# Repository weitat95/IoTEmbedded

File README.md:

View this project on [CADLAB.io](https://cadlab.io/project/1460). 

Project Files for ARM CORTEX M4, TM4C1234GH
Compiled and Programmed with Keil UVision 4

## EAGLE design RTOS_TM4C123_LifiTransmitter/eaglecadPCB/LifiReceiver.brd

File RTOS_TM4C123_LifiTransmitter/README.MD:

*  This is used for my BEng Honours 4th Year Project in The University of Edinburgh

*  Title: Demonstration of Visible Light Communication 
*
*  Author: Wei Tat Lee
*  Thesis Supervisor: Dr. Jonathan Terry

* This project builts on a previously developed RTOS in one of my classes(EE445M-Real-Time OS) in University of Texas, At Austin, taught by  Dr.Jonathan W. Valvano

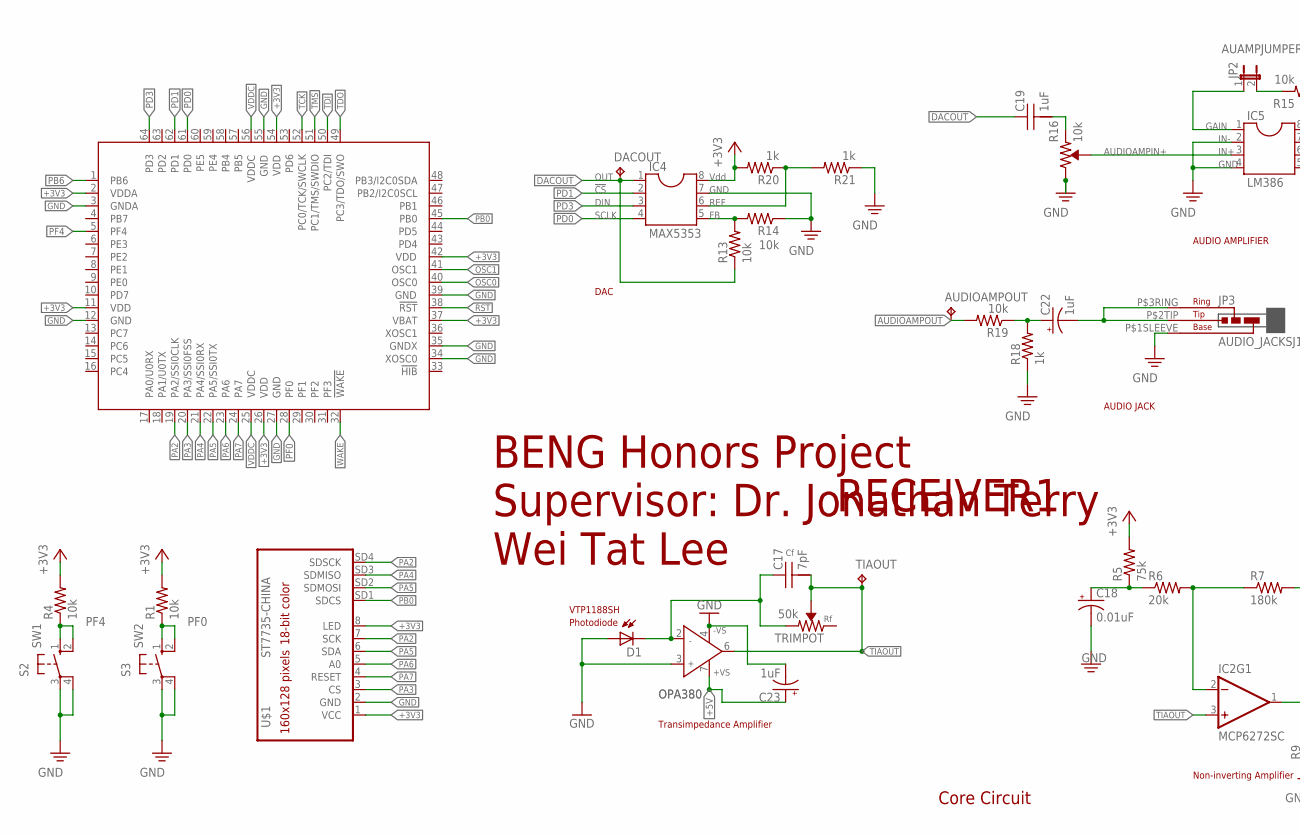
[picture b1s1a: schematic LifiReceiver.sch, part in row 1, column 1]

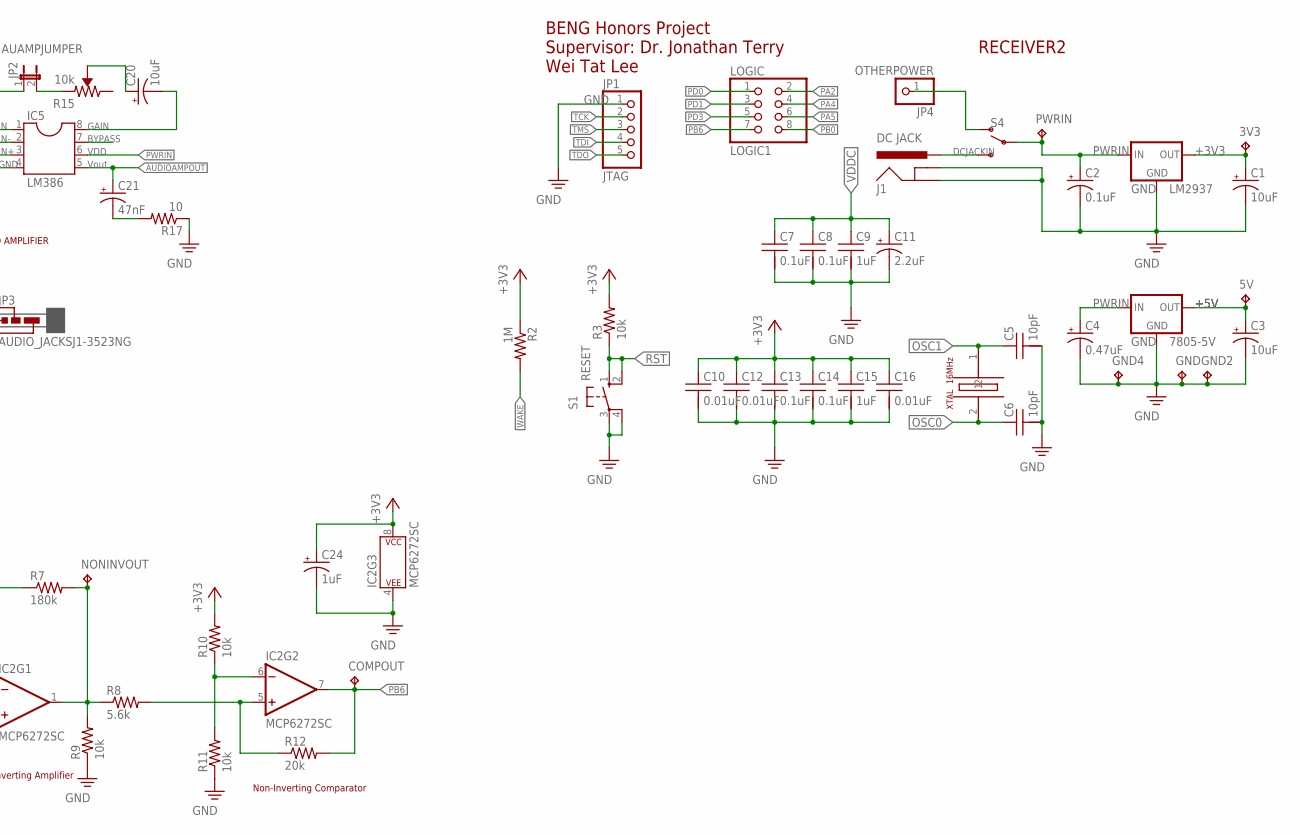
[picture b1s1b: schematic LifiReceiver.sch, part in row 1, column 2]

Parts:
3V3, 5V: TP_KEYSTONE500X; P1.1MM
7805-5V: 78XXS
AUDIOAMPOUT: TP_KEYSTONE500X; P1.1MM
C1, C3, C20: 10uF; CAP200MILPOLARIZED
C2: 0.1uF; CAP200MILPOLARIZED
C4: 0.47uF; CAP200MILPOLARIZED
C5, C6: 10pF; CAP100MIL
C7, C8, C13, C14: 0.1uF; CAP100MIL
C9, C15: 1uF; CAP100MIL
C10, C12, C16: 0.01uF; CAP100MIL
C11: 2.2uF; CAP200MILPOLARIZED
C17: 7pF; CAP200MIL
C18: 0.01uF; CAP200MILPOLARIZED
C19: 1uF; CAP200MIL
C21: 47nF; CAP200MILPOLARIZED
C22, C23, C24: 1uF; CAP200MILPOLARIZED
COMPOUT: TP_KEYSTONE500X; P1.1MM
D1: PHOTODIODE1X02THROUGH; 1X02_LOCK
DACOUT: TP_KEYSTONE500X; P1.1MM
GND, GND2, GND4: TP_KEYSTONE500X; P1.1MM
IC1: TM4C123[1,3,B]XXPM; PM_S-PQFP-G64
IC2: MCP6272SC; SOCKET-08
IC4: MAX5353; SOCKET-08
IC5: LM386; SOCKET-08
J1: DC JACK; POWER_JACK_PTH_BREAD
JP1: JTAG; 1X05
JP2: AUAMPJUMPER; 1X02
JP3: AUDIO_JACKSJ1-3523NG; JACK-SJ1-3523NG
JP4: OTHERPOWER; 1X01
LM2937: 78XXS
LOGIC: LOGIC1; 2X04
NONINVOUT: TP_KEYSTONE500X; P1.1MM
OPA380: AD820RM; MSOP08; MPN OPA380
PWRIN: TP_KEYSTONE500X; P1.1MM
R1, R3, R4, R9, R10, R11, R13, R14, R19: 10k; RES400MIL
R2: 1M; RES400MIL
R5: 75k; RES400MIL
R6, R12: 20k; RES400MIL
R7: 180k; RES400MIL
R8: 5.6k; RES400MIL
R15, R16: 10k; TRIM-SUNTAN3362P
R17: 10; RES400MIL
R18, R20, R21: 1k; RES400MIL
S1: RESET; B3F-10XX
S2: SW1; B3F-10XX
S3: SW2; B3F-10XX
S4: SWITCH-SPDT-PTH-11.6X4.0MM; SWITCH_SPDT_PTH_11.6X4.0MM
TIAOUT: TP_KEYSTONE500X; P1.1MM
TRIMPOT: 50k; TRIM-SUNTAN3362P
U$1: ST7735-CHINA
XTAL: 16MHz; XTAL

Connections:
+3V3: 3V3.TP, C1.+, C10.1, C12.1, C13.1, C14.1, C15.1, C16.1, C24.+, IC1.2 (VDDA), IC1.11 (VDD), IC1.26 (VDD), IC1.37 (VBAT), IC1.42 (VDD), IC1.54 (VDD), IC2.8 (P$V+), IC4.8, LM2937.OUT, R1.2, R2.1, R3.2, R4.2, R5.2, R10.2, R20.2, U$1.1 (VCC), U$1.8 (LED)
+5V: 5V.TP, 7805-5V.OUT, C3.+, C23.+, OPA380.7 (+VS)
AUAMPJUMP3: JP2.2, R15.P$1 (CCW)
AUAMPJUNCT1: C19.2, R16.P$1 (CCW)
AUAMPJUNCT2: C21.-, R17.2
AUAMPJUNCT4: C20.+, R15.P$2M (WIPER)
AUDIOAMPIN+: IC5.3, R16.P$2M (WIPER)
AUDIOAMPOUT: AUDIOAMPOUT.TP, C21.+, IC5.5, R19.2
AUDIOBYPASS: IC5.7
AUJACKJUNCT1: C22.+, R18.2, R19.1
AUJACKRINGTIP: C22.-, JP3.P$2TIP (TIP), JP3.P$3RING (RING)
COMPIN-: IC2.5 (+IN), R8.2, R12.1
COMPREF: IC2.6 (-IN), R10.1, R11.2
DACFB: IC4.5, R13.2, R14.2
DACOUT: C19.1, DACOUT.TP, IC4.1, R13.1
DACREF: IC4.6, R20.1, R21.2
DCJACKIN: J1.PWR, S4.3 (S)
GAIN1: IC5.1, JP2.1
GAIN2: C20.-, IC5.8
GND: 7805-5V.GND, C1.-, C2.-, C3.-, C4.-, C5.2, C6.2, C7.2, C8.2, C9.2, C10.2, C11.-, C12.2, C13.2, C14.2, C15.2, C16.2, C18.-, C23.-, C24.-, D1.1+ (A), GND.TP, GND2.TP, GND4.TP, IC1.3 (GNDA), IC1.12 (GND), IC1.27 (GND), IC1.34 (XOSC0), IC1.35 (GNDX), IC1.39 (GND), IC1.55 (GND), IC2.4 (P$V-), IC4.7, IC5.2, IC5.4, J1.GND, J1.GNDBREAK, JP1.1, JP3.P$1SLEEVE (BASE), LM2937.GND, OPA380.3 (IN+), OPA380.4 (-VS), R9.1, R11.1, R14.1, R16.P$3 (CW), R17.1, R18.1, R21.1, S1.3, S1.4 (P1), S2.3, S2.4 (P1), S3.3, S3.4 (P1), U$1.2 (GND)
NONINV-: IC2.2 (-IN), R6.2, R7.1
NONINVAMPJUNT1: C18.+, R5.1, R6.1
NONINVOUT: IC2.1 (OUT), NONINVOUT.TP, R7.2, R8.1, R9.2
OSC0: C6.1, IC1.40 (OSC0), XTAL.2
OSC1: C5.1, IC1.41 (OSC1), XTAL.1
OTHERPOWER: JP4.1, S4.1 (O)
PA2: IC1.19 (PA2/SSI0CLK), LOGIC.2, U$1.7 (SCK), U$1.SD4 (SDSCK)
PA3: IC1.20 (PA3/SSI0FSS), U$1.3 (CS)
PA4: IC1.21 (PA4/SSI0RX), LOGIC.4, U$1.SD3 (SDMISO)
PA5: IC1.22 (PA5/SSI0TX), LOGIC.6, U$1.6 (SDA), U$1.SD2 (SDMOSI)
PA6: IC1.23 (PA6), U$1.5 (A0)
PA7: IC1.24 (PA7), U$1.4 (RESET)
PB0: IC1.45 (PB0), LOGIC.8, U$1.SD1 (SDCS)
PB6: COMPOUT.TP, IC1.1 (PB6), IC2.7 (OUT), LOGIC.7, R12.2
PD0: IC1.61 (PD0), IC4.4, LOGIC.1
PD1: IC1.62 (PD1), IC4.2, LOGIC.3
PD3: IC1.64 (PD3), IC4.3, LOGIC.5
PF0: IC1.28 (PF0), R1.1, S3.1 (S), S3.2 (S1)
PF4: IC1.5 (PF4), R4.1, S2.1 (S), S2.2 (S1)
PHOTODIODECAT: C17.1, D1.2 (C), OPA380.2 (IN-), TRIMPOT.P$1 (CCW)
PWRIN: 7805-5V.IN, C2.+, C4.+, IC5.6, LM2937.IN, PWRIN.TP, S4.2
RST: IC1.38 (!RST), R3.1, S1.1 (S), S1.2 (S1)
TCK: IC1.52 (PC0/TCK/SWCLK), JP1.2
TDI: IC1.50 (PC2/TDI), JP1.4
TDO: IC1.49 (PC3/TDO/SWO), JP1.5
TIAOUT: C17.2, IC2.3 (+IN), OPA380.6 (OUT), TIAOUT.TP, TRIMPOT.P$2M (WIPER)
TMS: IC1.51 (PC1/TMS/SWDIO), JP1.3
VDDC: C7.1, C8.1, C9.1, C11.+, IC1.25 (VDDC), IC1.56 (VDDC)
WAKE: IC1.32 (!WAKE), R2.2

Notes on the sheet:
BENG Honors Project Supervisor: Dr. Jonathan Terry Wei Tat Lee
Transimpedance Amplifier
Non-inverting Amplifier
Non-Inverting Comparator
Photodiode
VTP1188SH
Core Circuit
!CS
DIN
SCLK
OUT
Vdd
GND
REF
DAC
BYPASS
IN-
IN+
GAIN
VDD
Vout
AUDIO AMPLIFIER
AUDIO JACK
RECEIVER2
RECEIVER1

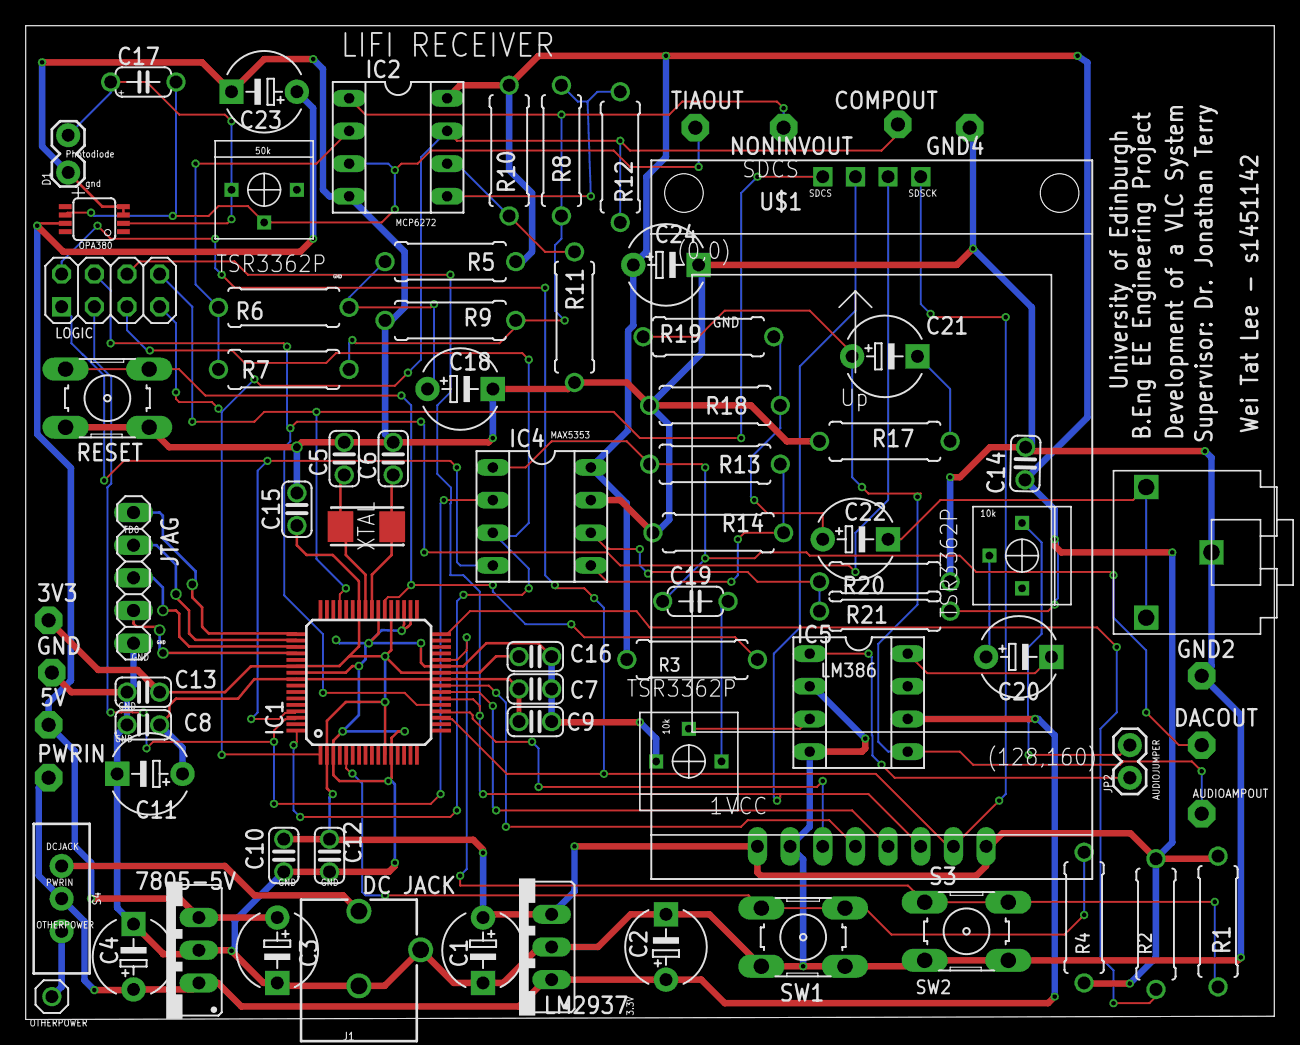
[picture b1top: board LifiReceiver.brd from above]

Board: 2 copper layers, 97.1 x 77.3 mm, 77 parts (0 on the bottom side), 48 nets.

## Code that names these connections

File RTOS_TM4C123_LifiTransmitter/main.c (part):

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//*****************************************************************************
//***************************** Connections ***********************************
/*
// IF YOU ARE USING THE LAUNCHPAD VERSION, PLEASE NOTE THAT PD0 and PB6 ARE INTERNALLY CONNECTED 
// THE DAC uses PD0 and Edge Capture uses PB6 which would cause HARD FAILURE
// EDGE CAPTURE TIMER uses this connection to DEBUG EDGE CAPTURE in particular

******Transmitter******
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******Receiver*********
ADCSampler- GPIO PD2 
or
EDGECAPTURE- GPIO PB6
******ST7735***
VCC 			- 3.3V
GND 			- GND
CS  			- PA3
RESET 		- PA7
A0(DATA)	- PA6
SDA(MOSI)	- PA5
SCK				-PA2
LED				-3.3V
*******SDCARD**********
SDCS      - PB0
SDMOSI		- PA5
SDMISO		- PA4
SDSCK			- PA2
******DAC*******
SSI1Clk (SCLK, pin 4) connected to PD0
SSI1Fss (!CS, pin 2) connected to PD1
SSI1Tx (DIN, pin 3) connected to PD3
******Switch****

*/
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To program the emitter for the LIFI please define emitter below
to program the receiver for the LIFI please define receiver below
*/
//REMEMBER TO CHANGE (ST7735.c)SDCS PB0 for TRANSMITTER And PD7 FOR RECEIVER
//#define EMITTER
#define RECEIVER

//************************ CORE FEATURES *************************************
// Only 2 type of options for the Receiver 
// (1) ADC Sampling - PD2 (Configured Below)
// (2) Edge Input Capture Timer - PB6             **A more stable version**

#ifdef RECEIVER
	#define ADCSAMPLING 0
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	#define EDGETIMERMODE 1
		//Edge capture is used instead of using ADC sampling
		#if (EDGETIMERMODE)&&(!AUDIOOUT)
			#define EDGETIMERDEBUG 0 	//using PD0 to debug edge timer,
															//DAC is also using PD0
															//Cannot activate both at the same time
			#define AUTODETECTSPEED 1 //Auto Detect Transmitting Frequency
	#endif
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#define PB3       (*((volatile unsigned long *)0x40005020))

// PORT F - Memory Mapped GPIO
#define PF0       (*((volatile uint32_t *)0x40025004))
#define PF1       (*((volatile uint32_t *)0x40025008))
#define PF2       (*((volatile uint32_t *)0x40025010))
#define PF3       (*((volatile uint32_t *)0x40025020))
#define PF4       (*((volatile uint32_t *)0x40025040))

uint32_t NumCreated;   // number of foreground threads created
uint32_t NumSamples;   // incremented every sample
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int myi=0;
#define BUFFFSIZE 1024
unsigned long bufff[BUFFFSIZE];
//Main task for edge capture on PB6
//1 Rising Edge
//2 Rising Edge Long
//3 Falling Edge
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		}
	}
}
//Debugging task to simulate square waves in PB6 by toggling PD0 since they are connected by R9;
void pulsePD0(void){
	int n=0;
	while(n<100){
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	#if EDGETIMERMODE
		//EdgeTimer_Init(&edgeTask);
		#if EDGETIMERDEBUG	
			//Activate Port D for simulating squarewaves to test edge capture to PB6
			SYSCTL_RCGCGPIO_R |= 0x08; // activate Port D
			while((SYSCTL_PRGPIO_R&0x08) == 0){};// allow time to finish activating
			GPIO_PORTD_DIR_R |= 0x01;  // make PD0 out
			GPIO_PORTD_AFSEL_R &= ~0x01;// disable alt funct on PD0
			GPIO_PORTD_DEN_R |= 0x01;  // enable digital I/O on PD0
															 // configure PD0 as GPIO
			GPIO_PORTD_PCTL_R = (GPIO_PORTD_PCTL_R&0xFFFFFFF0)+0x00000000;
			GPIO_PORTD_AMSEL_R &= ~0x01;// disable analog functionality on PD0
			GPIO_PORTD_DATA_R = 0;
		#endif
	#endif
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
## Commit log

2017-05-12 inititalizing folder
2017-05-23 added espflasher
2017-05-23 fixing
2017-05-23 add iot demoday
2017-05-23 fixed esp conenctions and removed reset
2017-05-29 added clean RTOS project, starting IOT with RTOS
2017-05-29 added esp module
2017-05-29 added bluetooth module, havent test yet, esp module buggy
2017-05-29 fixed os sw functions
2017-05-30 added bluetooth module
2017-06-10 added valvano's led project
2017-06-10 Added LED Ring interfacing and BMP280, need calibration
2018-01-17 init LIFI project
2018-01-28 debugging LIFI Emitter
2018-02-05 add LifiReceiver functionality to decode Manchester Encoding
2018-03-07 Add Lab4 files to test FAT32 File System Interfacing
2018-03-15 Add debugging function to test software functionality taking inputs from hard coded buffer
2018-03-17 Add simulation without real data being sampled, fix synchronisation issues with wordDetect thread and consumerThread
2018-03-18 fix receiver using oversampling factor properly
2018-03-18 make oversampling to be dynamic instead of a constant
2018-03-26 Add DAC module as AUDIOOUT
2018-03-26 add FAT32 FileSystem
2018-04-01 checkpoint before starting audio output
2018-04-01 add helix source code into project
2018-04-03 Use Input Capture for Falling edge and Rising Edge instead
2018-04-03 Add define statement to remove clashes of PD0 between edgedebug and AUDIO DAC
2018-04-04 checkA
2018-04-05 fix bug with comparator, add changing threshold and changing transmitting freq in interpreter
2018-04-05 fix auto detect speed transmitter buf
2018-04-05 add header on main.c and clean code
2018-04-05 another cleanup
2018-04-06 Add more SDCARD tests, test (READTOWRITE) with copying 1MBytes
2018-04-06 Fix Interpretor bug
2018-04-24 checkpoint before adding fs application
2018-04-25 Eagle Cad PCB source code
2018-04-25 Create file1
2018-05-15 ReadFileTransmit to ST7735,EdgeCapture and SDCS conflict, have to switch SDCS commands
2018-05-16 Calibrate Sending Speed, pre viva
2018-11-22 Backlink to CADLAB.io has been added.

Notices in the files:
parts and their libraries:
SparkFun-Connectors: Licensing: Creative Commons ShareAlike 4.0 International - https://creativecommons.org/licenses/by-sa/4.0
